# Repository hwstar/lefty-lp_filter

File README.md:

# Lefty-lp_filter
Lefty 8 Band Low Pass filter board

This is an 8 band low pass filter board for the Lefty Transceiver.

The schematic capture and pwb layout was originally done in KiCAD 5 and migrated to KiCAD 6.

The filters are individually selectable via an I2C port expander.

The filter topology used in the design is:

"Second-Harmonic Optimized Low Pass Filters" by Ed Wetherhold, W3NQN
https://www.arrl.org/files/file/Technology/tis/info/pdf/9902044.pdf

The pdf schematic file is: lp_filter_8_bands.pdf

The BOM file is: lp_filter_8_bands_BOM.csv

The gerber files are in the directory LPF_X4_FAB.

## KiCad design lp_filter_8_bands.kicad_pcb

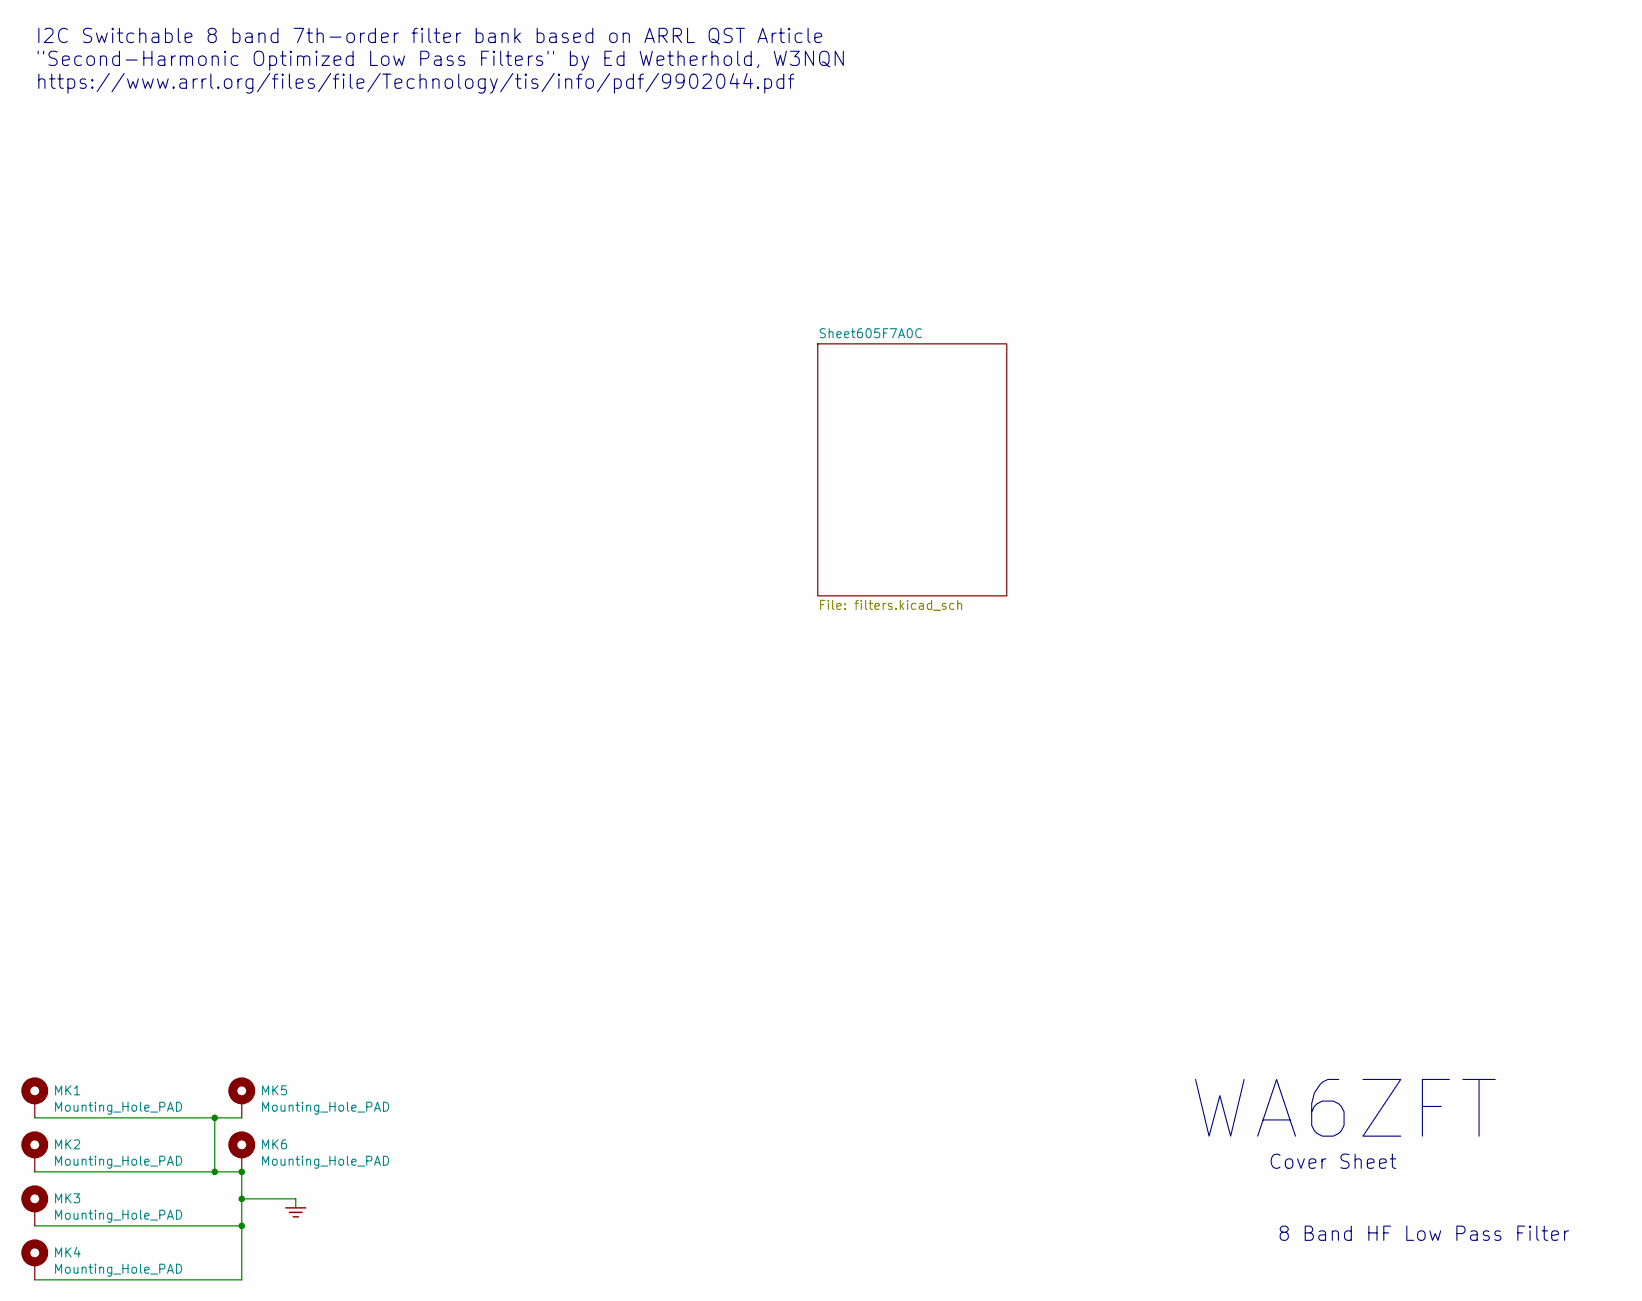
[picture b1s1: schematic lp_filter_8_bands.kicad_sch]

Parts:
MK1, MK2, MK3, MK4, MK5, MK6: Mounting_Hole_PAD; MountingHole_3.5mm_Pad_Via

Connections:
GND: MK1.1, MK2.1, MK3.1, MK4.1, MK5.1, MK6.1; also elsewhere on the board

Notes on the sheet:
WA6ZFT
Cover Sheet
I2C Switchable 8 band 7th-order filter bank based on ARRL QST Article "Second-Harmonic Optimized Low Pass Filters" by Ed Wetherhold, W3NQN https://www.arrl.org/files/file/Technology/tis/info/pdf/9902044.pdf
8 Band HF Low Pass Filter

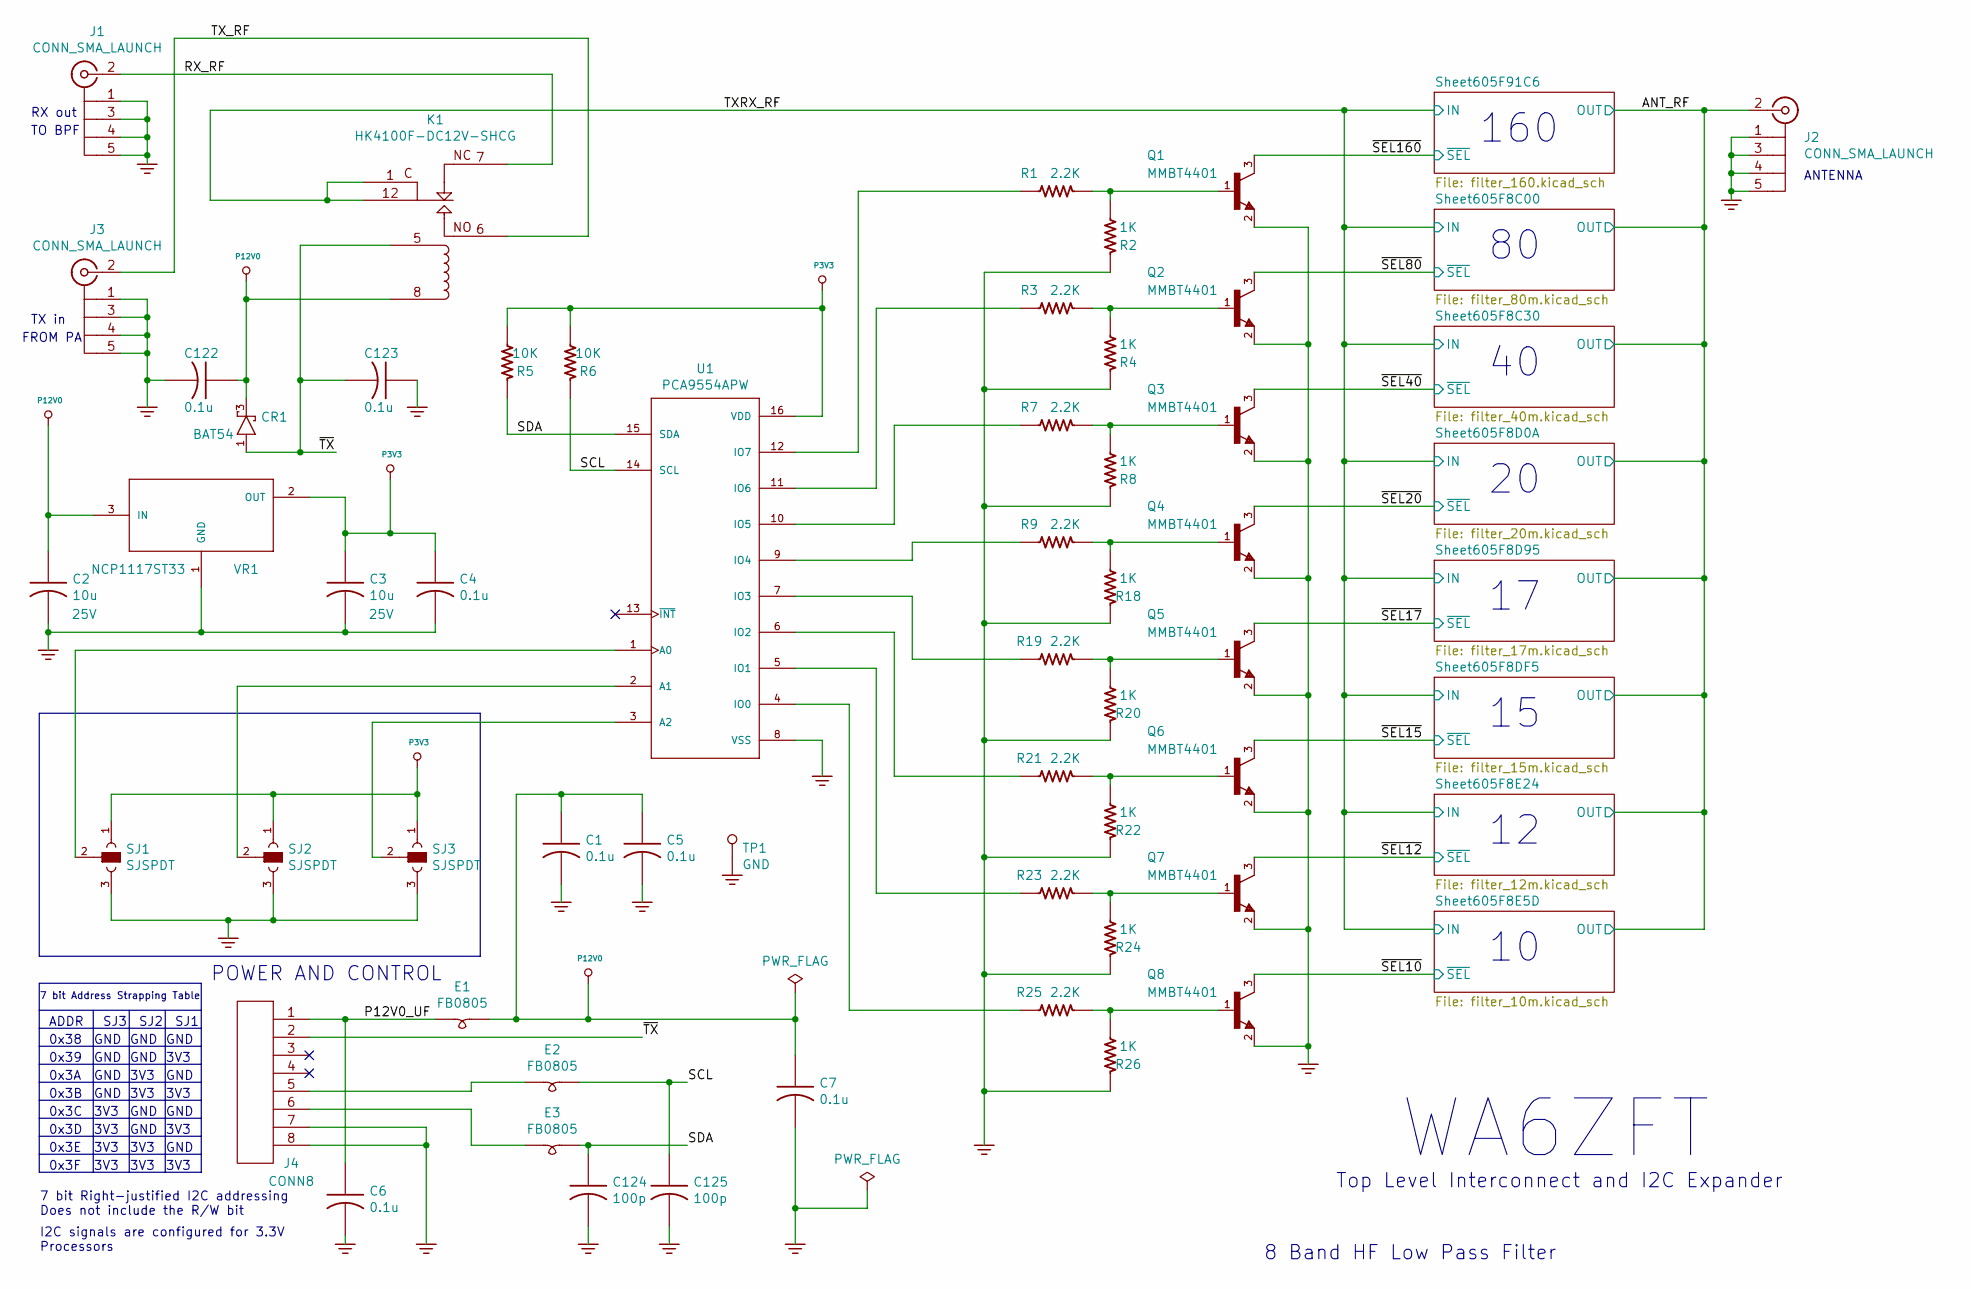
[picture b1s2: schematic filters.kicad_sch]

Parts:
C1, C4, C5, C6, C7, C122, C123: 0.1u; CC0805; PartNumber 800063-XXX
C2, C3: 10u; CC1206; Voltage 25V; PartNumber 800063-XXX
C124, C125: 100p; CC0805; PartNumber 800063-XXX
CR1: BAT54; SOT23-3-SAR-V2; PartNumber 800127-101
E1, E2, E3: FB0805; L_0805_2012Metric_Pad1.05x1.20mm_HandSolder; PartNumber 80000X-XXX
J1, J2, J3: CONN_SMA_LAUNCH; SMA_Launch_Kinghelm_KH-SMA-KE8-G; PartNumber 800233-101
J4: CONN8; JST_B8B_XH_A; PartNumber 800114-108
K1: HK4100F-DC12V-SHCG; RELAY_HK4100; PartNumber 800231-101
Q1, Q2, Q3, Q4, Q5, Q6, Q7, Q8: MMBT4401; SOT23-3-SAR-V2; PartNumber 800110-101
R1, R3, R7, R9, R19, R21, R23, R25: 2.2K; RC0805; PartNumber 800XXX-XXX
R2, R4, R8, R18, R20, R22, R24, R26: 1K; RC0805; PartNumber 800XXX-XXX
R5, R6: 10K; RC0805; PartNumber 800XXX-XXX
SJ1, SJ2, SJ3: SJSPDT
TP1: GND; TESTPIN; PartNumber 800116-101
U1: PCA9554APW; TSSOP-16_4.4x5mm_P0.65mm; PartNumber 800237-101
VR1: NCP1117ST33; SOT-223-3_TabPin2; PartNumber 800121-101

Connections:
/Sheet605F7A0C/ANT_RF: J2.2; also elsewhere on the board
/Sheet605F7A0C/P12V0_UF: C6.1, E1.1, J4.1
/Sheet605F7A0C/RX_RF: J1.2, K1.7
/Sheet605F7A0C/SCL: C125.1, E2.2, R6.1, U1.14 (SCL)
/Sheet605F7A0C/SDA: C124.1, E3.2, R5.1, U1.15 (SDA)
/Sheet605F7A0C/TXRX_RF: K1.1, K1.12; also elsewhere on the board
/Sheet605F7A0C/TX_RF: J3.2, K1.6
/Sheet605F7A0C/~SEL10: Q8.3 (C); also elsewhere on the board
/Sheet605F7A0C/~SEL12: Q7.3 (C); also elsewhere on the board
/Sheet605F7A0C/~SEL15: Q6.3 (C); also elsewhere on the board
/Sheet605F7A0C/~SEL17: Q5.3 (C); also elsewhere on the board
/Sheet605F7A0C/~SEL20: Q4.3 (C); also elsewhere on the board
/Sheet605F7A0C/~SEL40: Q3.3 (C); also elsewhere on the board
/Sheet605F7A0C/~SEL80: Q2.3 (C); also elsewhere on the board
/Sheet605F7A0C/~SEL160: Q1.3 (C); also elsewhere on the board
/Sheet605F7A0C/~TX: C123.2, CR1.1 (A), J4.2, K1.5
GND: C1.2, C2.2, C3.2, C4.2, C5.2, C6.2, C7.2, C122.2, C123.1, C124.2, C125.2, J1.1, J1.3, J1.4, J1.5, J2.1, J2.3, J2.4, J2.5, J3.1, J3.3, J3.4, J3.5, J4.7, J4.8, Q1.2 (E), Q2.2 (E), Q3.2 (E), Q4.2 (E), Q5.2 (E), Q6.2 (E), Q7.2 (E), Q8.2 (E), R2.1, R4.1, R8.1, R18.1, R20.1, R22.1, R24.1, R26.1, SJ1.3, SJ2.3, SJ3.3, TP1.1 (TP), U1.8 (VSS), VR1.1 (GND); also elsewhere on the board
unnamed: E2.1, J4.5
unnamed: E3.1, J4.6
unnamed: Q1.1 (B), R1.1, R2.2
unnamed: Q2.1 (B), R3.1, R4.2
unnamed: Q3.1 (B), R7.1, R8.2
unnamed: Q4.1 (B), R9.1, R18.2
unnamed: Q5.1 (B), R19.1, R20.2
unnamed: Q6.1 (B), R21.1, R22.2
unnamed: Q7.1 (B), R23.1, R24.2
unnamed: Q8.1 (B), R25.1, R26.2
unnamed: R1.2, U1.12 (IO7)
unnamed: R3.2, U1.11 (IO6)
unnamed: R7.2, U1.10 (IO5)
unnamed: R9.2, U1.9 (IO4)
unnamed: R19.2, U1.7 (IO3)
unnamed: R21.2, U1.6 (IO2)
unnamed: R23.2, U1.5 (IO1)
unnamed: R25.2, U1.4 (IO0)
unnamed: SJ1.2, U1.1 (A0)
unnamed: SJ2.2, U1.2 (A1)
unnamed: SJ3.2, U1.3 (A2)
P3V3: C3.1, C4.1, R5.2, R6.2, SJ1.1, SJ2.1, SJ3.1, U1.16 (VDD), VR1.2 (OUT)
P12V0: C1.1, C2.1, C5.1, C7.1, C122.1, CR1.3 (C), E1.2, K1.8, VR1.3 (IN); also elsewhere on the board

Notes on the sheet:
GND
SJ2
3V3
0x3A
0x3E
0x3B
0x39
0x3D
ADDR
160
8 Band HF Low Pass Filter
7 bit Address Strapping Table
TX in
SJ3
I2C signals are configured for 3.3V Processors
Top Level Interconnect and I2C Expander
RX out
GND
7 bit Right-justified I2C addressing Does not include the R/W bit
0x3F
WA6ZFT
SJ1
0x38
FROM PA
POWER AND CONTROL
TO BPF
0x3C
ANTENNA

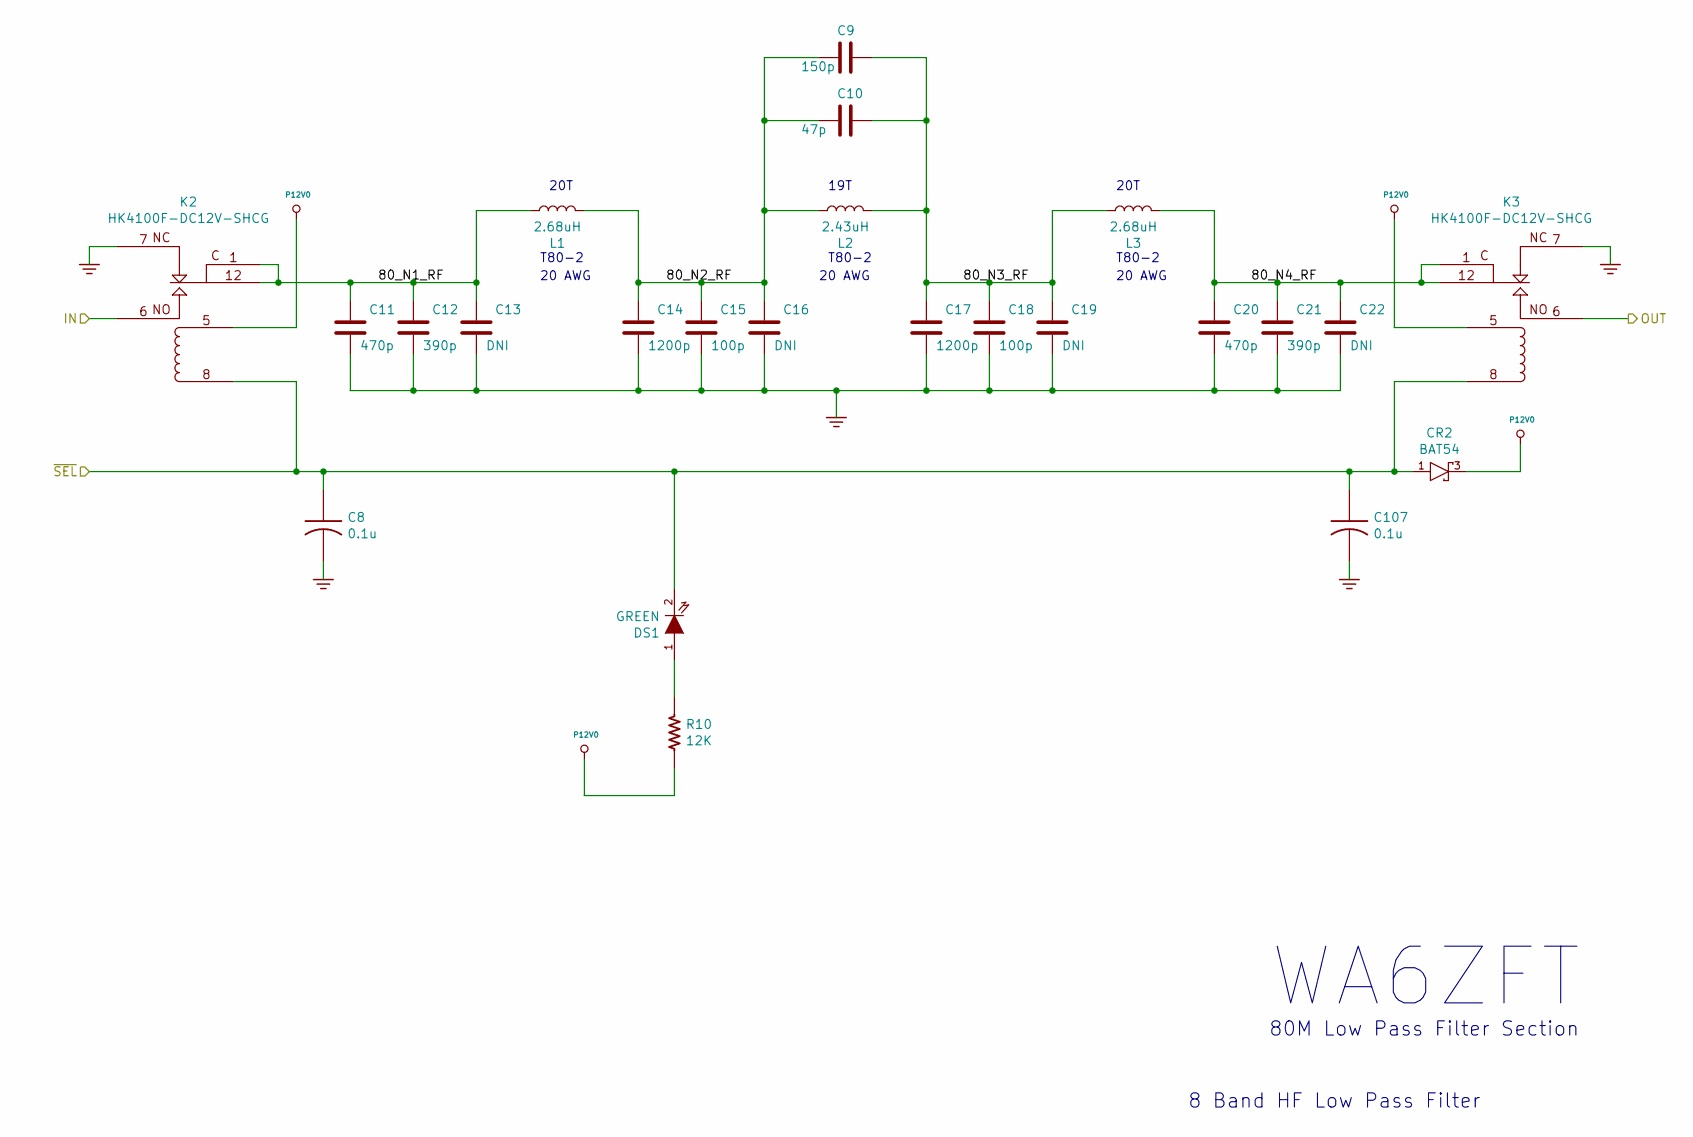
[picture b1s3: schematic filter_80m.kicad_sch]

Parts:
C8, C107: 0.1u; CC0805; PartNumber 800063-XXX
C9: 150p; CC0805; PartNumber 800232-151
C10: 47p; CC0805; PartNumber 800232-470
C11, C20: 470p; CC0805; PartNumber 800232-471
C12, C21: 390p; CC0805; PartNumber 800232-391
C13, C16, C19, C22: DNI; CC0805; PartNumber 800XXX-XXX
C14, C17: 1200p; CC0805; PartNumber 800232-122
C15, C18: 100p; CC0805; PartNumber 800232-101
CR2: BAT54; SOT23-3-SAR-V2; PartNumber 800127-101
DS1: GREEN; LED0805; PartNumber 800113-102
K2, K3: HK4100F-DC12V-SHCG; RELAY_HK4100; PartNumber 800231-101
L1, L3: 2.68uH; TOROID_T80_VERT; PartNumber 800234-802
L2: 2.43uH; TOROID_T80_VERT; PartNumber 800234-802
R10: 12K; RC0805; PartNumber 800XXX-XXX

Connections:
/Sheet605F7A0C/ANT_RF: K3.6; also elsewhere on the board
/Sheet605F7A0C/Sheet605F8C00/80_N1_RF: C11.1, C12.1, C13.1, K2.1, K2.12, L1.1
/Sheet605F7A0C/Sheet605F8C00/80_N2_RF: C9.2, C10.2, C14.1, C15.1, C16.1, L1.2, L2.1
/Sheet605F7A0C/Sheet605F8C00/80_N3_RF: C9.1, C10.1, C17.1, C18.1, C19.1, L2.2, L3.1
/Sheet605F7A0C/Sheet605F8C00/80_N4_RF: C20.1, C21.1, C22.1, K3.1, K3.12, L3.2
/Sheet605F7A0C/TXRX_RF: K2.6; also elsewhere on the board
/Sheet605F7A0C/~SEL80: C8.1, C107.1, CR2.1 (A), DS1.2 (K), K2.8, K3.8; also elsewhere on the board
GND: C8.2, C11.2, C12.2, C13.2, C14.2, C15.2, C16.2, C17.2, C18.2, C19.2, C20.2, C21.2, C22.2, C107.2, K2.7, K3.7; also elsewhere on the board
unnamed: DS1.1 (A), R10.1
P12V0: CR2.3 (C), K2.5, K3.5, R10.2; also elsewhere on the board

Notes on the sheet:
20 AWG
20T
8 Band HF Low Pass Filter
T80-2
19T
80M Low Pass Filter Section
WA6ZFT

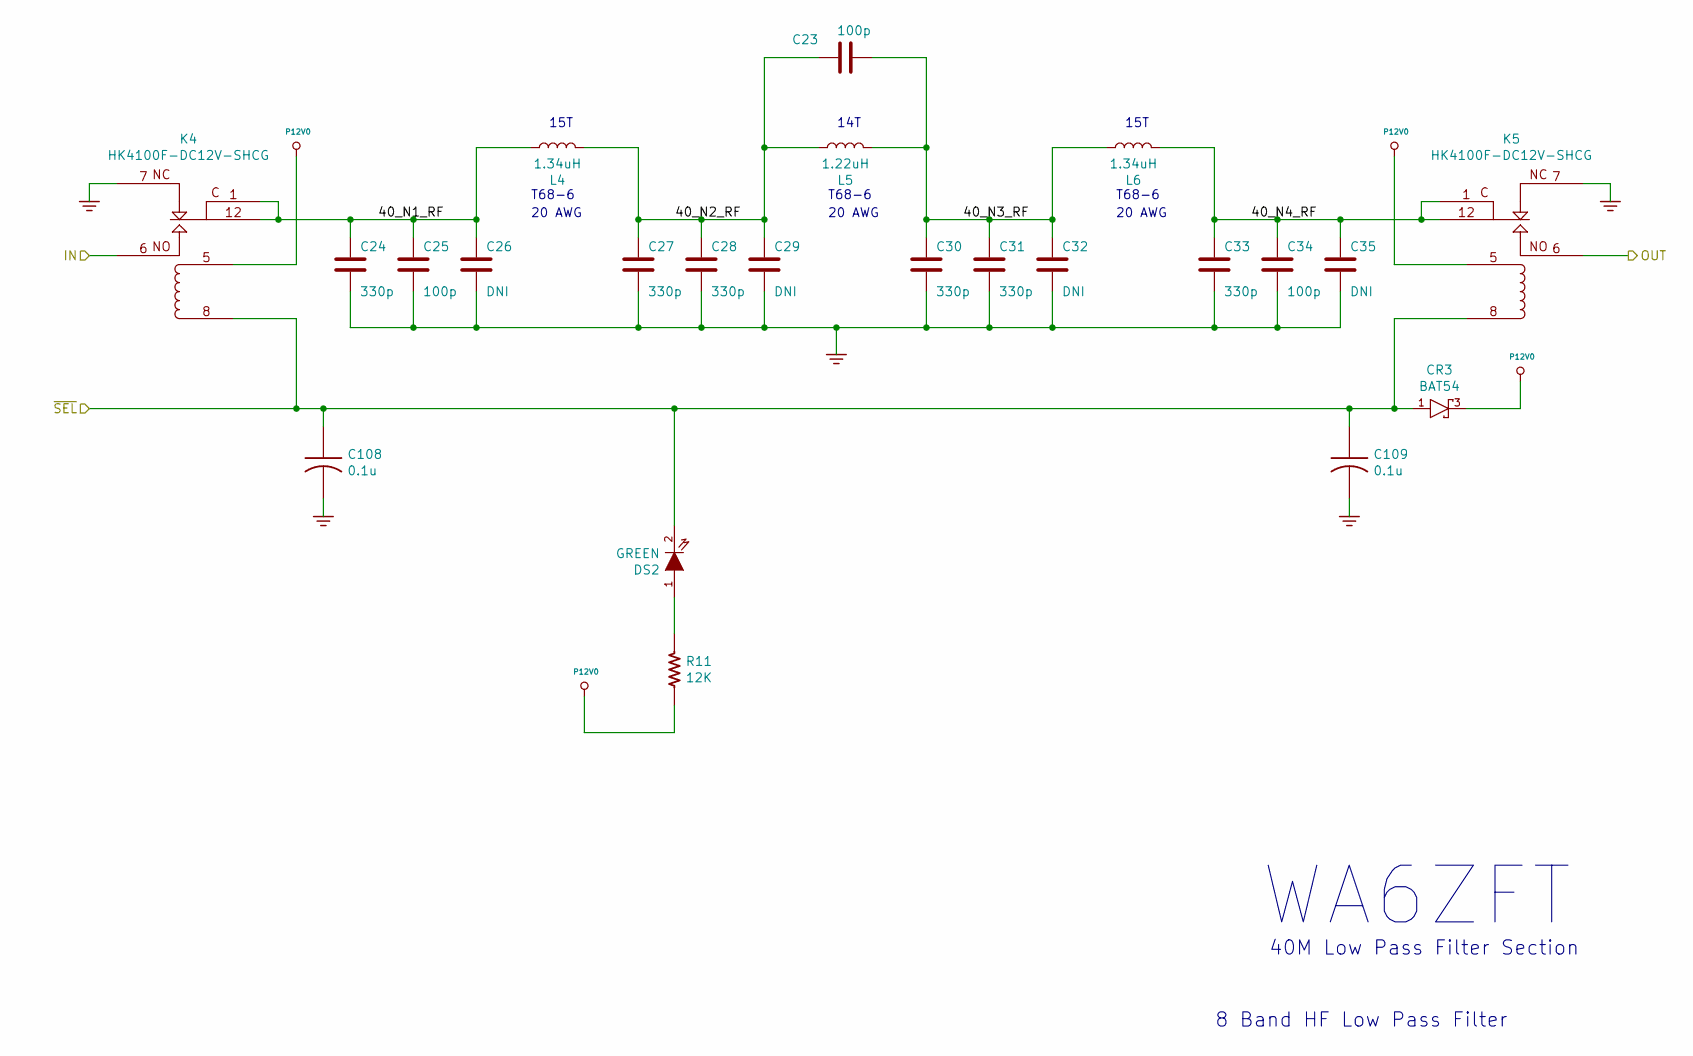
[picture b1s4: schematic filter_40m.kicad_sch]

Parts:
C23, C25, C34: 100p; CC0805; PartNumber 800232-101
C24, C27, C28, C30, C31, C33: 330p; CC0805; PartNumber 800232-331
C26, C29, C32, C35: DNI; CC0805; PartNumber 800XXX-XXX
C108, C109: 0.1u; CC0805; PartNumber 800063-XXX
CR3: BAT54; SOT23-3-SAR-V2; PartNumber 800127-101
DS2: GREEN; LED0805; PartNumber 800113-102
K4, K5: HK4100F-DC12V-SHCG; RELAY_HK4100; PartNumber 800231-101
L4, L6: 1.34uH; TOROID_T68_VERT; PartNumber 800234-686
L5: 1.22uH; TOROID_T68_VERT; PartNumber 800234-686
R11: 12K; RC0805; PartNumber 800XXX-XXX

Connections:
/Sheet605F7A0C/ANT_RF: K5.6; also elsewhere on the board
/Sheet605F7A0C/Sheet605F8C30/40_N1_RF: C24.1, C25.1, C26.1, K4.1, K4.12, L4.1
/Sheet605F7A0C/Sheet605F8C30/40_N2_RF: C23.2, C27.1, C28.1, C29.1, L4.2, L5.1
/Sheet605F7A0C/Sheet605F8C30/40_N3_RF: C23.1, C30.1, C31.1, C32.1, L5.2, L6.1
/Sheet605F7A0C/Sheet605F8C30/40_N4_RF: C33.1, C34.1, C35.1, K5.1, K5.12, L6.2
/Sheet605F7A0C/TXRX_RF: K4.6; also elsewhere on the board
/Sheet605F7A0C/~SEL40: C108.1, C109.1, CR3.1 (A), DS2.2 (K), K4.8, K5.8; also elsewhere on the board
GND: C24.2, C25.2, C26.2, C27.2, C28.2, C29.2, C30.2, C31.2, C32.2, C33.2, C34.2, C35.2, C108.2, C109.2, K4.7, K5.7; also elsewhere on the board
unnamed: DS2.1 (A), R11.1
P12V0: CR3.3 (C), K4.5, K5.5, R11.2; also elsewhere on the board

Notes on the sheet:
T68-6
40M Low Pass Filter Section
15T
8 Band HF Low Pass Filter
20 AWG
WA6ZFT
14T
15T

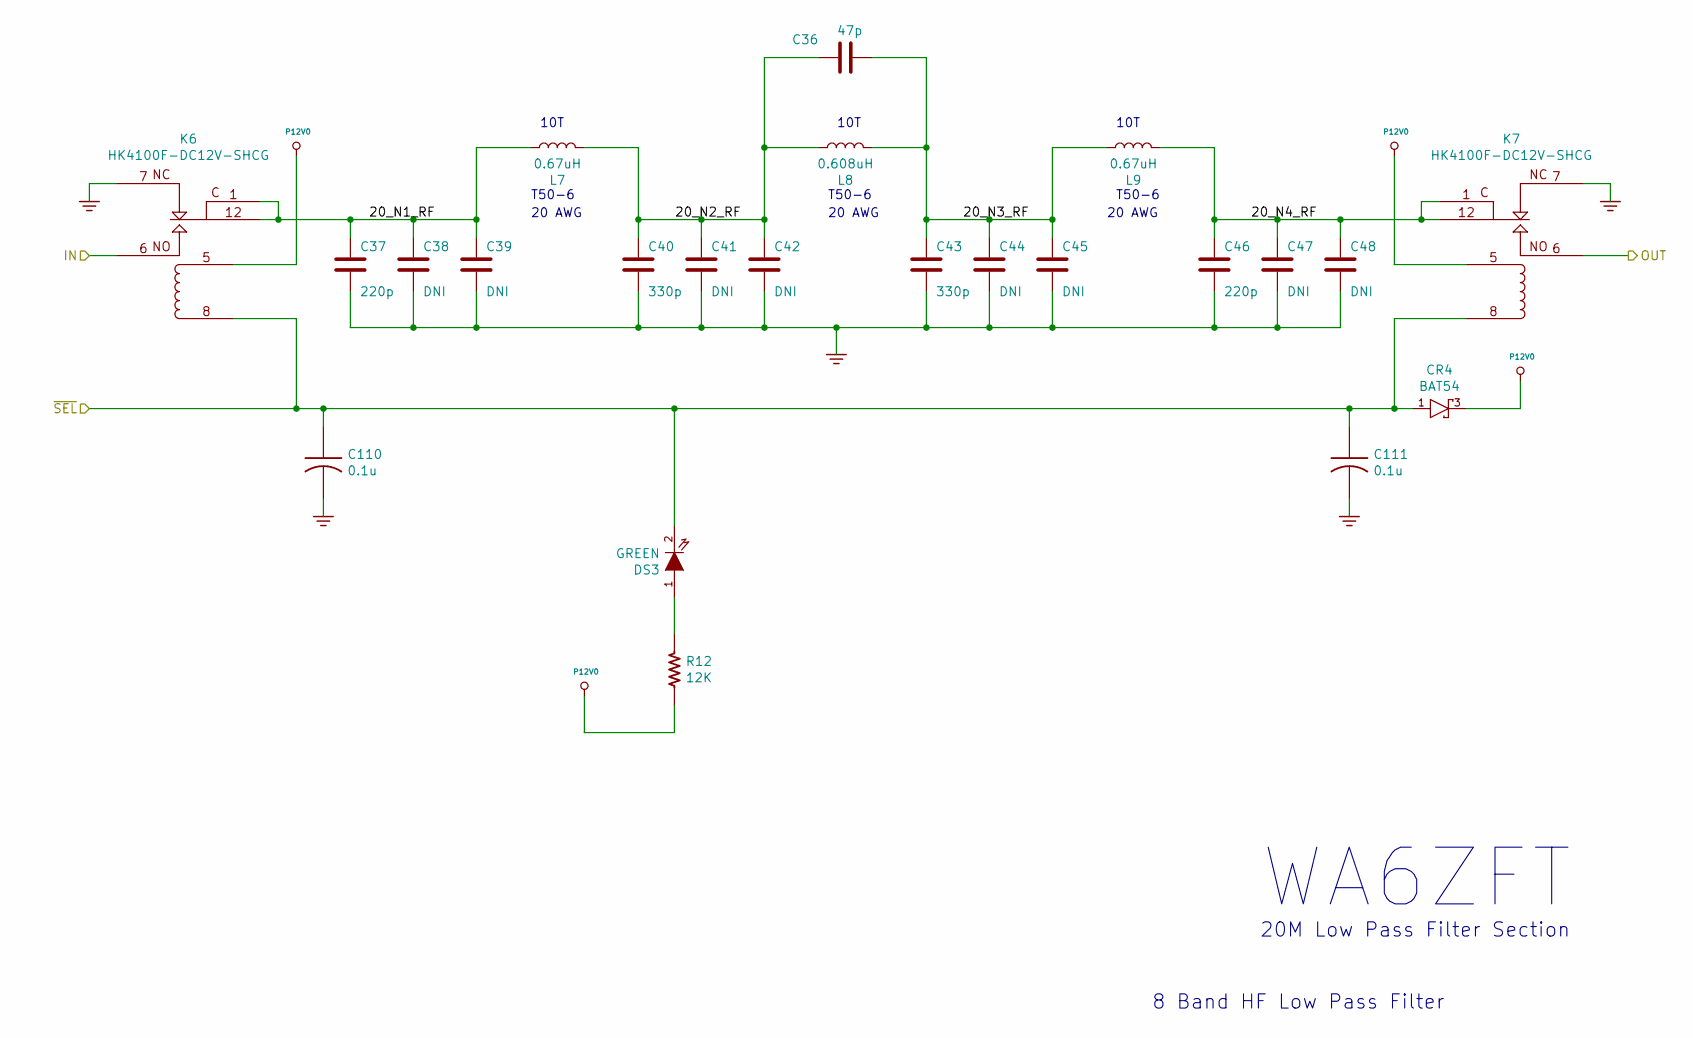
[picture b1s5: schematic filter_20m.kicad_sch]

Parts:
C36: 47p; CC0805; PartNumber 800232-470
C37, C46: 220p; CC0805; PartNumber 800232-221
C38, C39, C41, C42, C44, C45, C47, C48: DNI; CC0805; PartNumber 800XXX-XXX
C40, C43: 330p; CC0805; PartNumber 800232-331
C110, C111: 0.1u; CC0805; PartNumber 800063-XXX
CR4: BAT54; SOT23-3-SAR-V2; PartNumber 800127-101
DS3: GREEN; LED0805; PartNumber 800113-102
K6, K7: HK4100F-DC12V-SHCG; RELAY_HK4100; PartNumber 800231-101
L7, L9: 0.67uH; TOROID_T50_VERT; PartNumber 800234-506
L8: 0.608uH; TOROID_T50_VERT; PartNumber 800234-506
R12: 12K; RC0805; PartNumber 800XXX-XXX

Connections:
/Sheet605F7A0C/ANT_RF: K7.6; also elsewhere on the board
/Sheet605F7A0C/Sheet605F8D0A/20_N1_RF: C37.1, C38.1, C39.1, K6.1, K6.12, L7.1
/Sheet605F7A0C/Sheet605F8D0A/20_N2_RF: C36.2, C40.1, C41.1, C42.1, L7.2, L8.1
/Sheet605F7A0C/Sheet605F8D0A/20_N3_RF: C36.1, C43.1, C44.1, C45.1, L8.2, L9.1
/Sheet605F7A0C/Sheet605F8D0A/20_N4_RF: C46.1, C47.1, C48.1, K7.1, K7.12, L9.2
/Sheet605F7A0C/TXRX_RF: K6.6; also elsewhere on the board
/Sheet605F7A0C/~SEL20: C110.1, C111.1, CR4.1 (A), DS3.2 (K), K6.8, K7.8; also elsewhere on the board
GND: C37.2, C38.2, C39.2, C40.2, C41.2, C42.2, C43.2, C44.2, C45.2, C46.2, C47.2, C48.2, C110.2, C111.2, K6.7, K7.7; also elsewhere on the board
unnamed: DS3.1 (A), R12.1
P12V0: CR4.3 (C), K6.5, K7.5, R12.2; also elsewhere on the board

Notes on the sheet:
20 AWG
WA6ZFT
10T
20M Low Pass Filter Section
T50-6
8 Band HF Low Pass Filter
10T

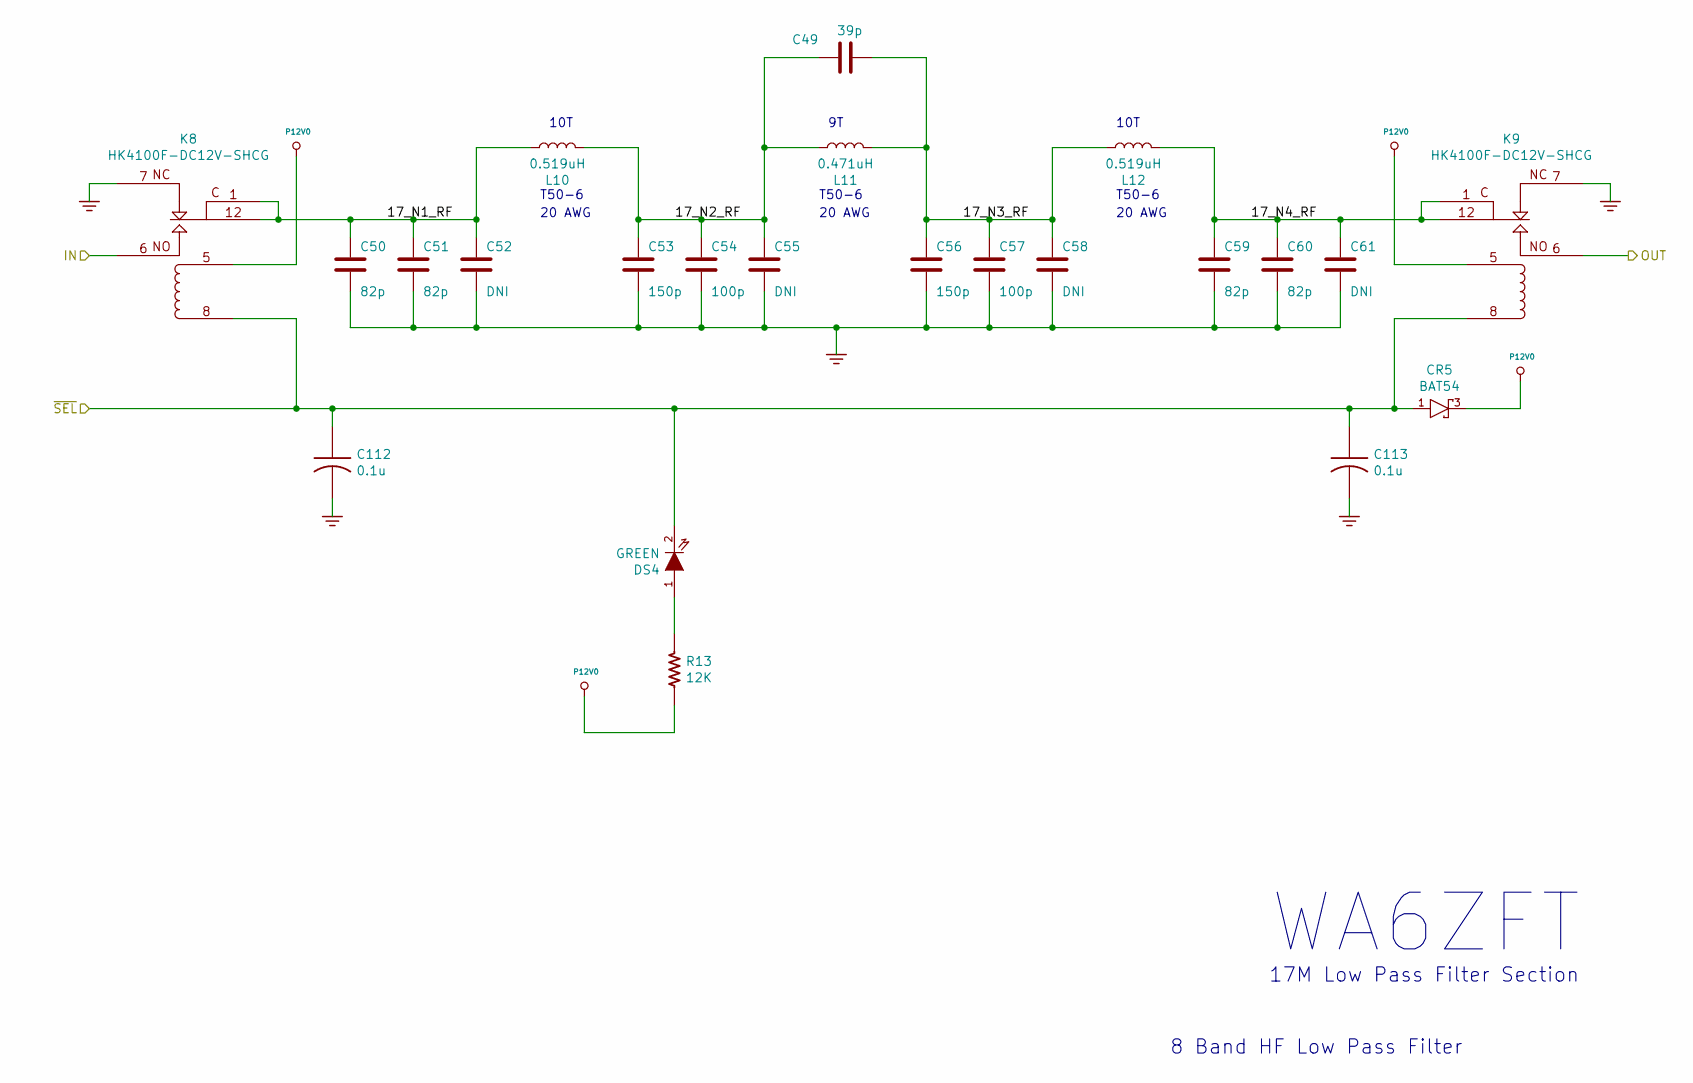
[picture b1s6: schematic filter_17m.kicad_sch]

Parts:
C49: 39p; CC0805; PartNumber 800232-390
C50, C51, C59, C60: 82p; CC0805; PartNumber 800232-820
C52, C55, C58, C61: DNI; CC0805; PartNumber 800XXX-XXX
C53, C56: 150p; CC0805; PartNumber 800232-151
C54, C57: 100p; CC0805; PartNumber 800232-101
C112, C113: 0.1u; CC0805; PartNumber 800063-XXX
CR5: BAT54; SOT23-3-SAR-V2; PartNumber 800127-101
DS4: GREEN; LED0805; PartNumber 800113-102
K8, K9: HK4100F-DC12V-SHCG; RELAY_HK4100; PartNumber 800231-101
L10, L12: 0.519uH; TOROID_T50_VERT; PartNumber 800234-506
L11: 0.471uH; TOROID_T50_VERT; PartNumber 800234-506
R13: 12K; RC0805; PartNumber 800XXX-XXX

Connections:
/Sheet605F7A0C/ANT_RF: K9.6; also elsewhere on the board
/Sheet605F7A0C/Sheet605F8D95/17_N1_RF: C50.1, C51.1, C52.1, K8.1, K8.12, L10.1
/Sheet605F7A0C/Sheet605F8D95/17_N2_RF: C49.2, C53.1, C54.1, C55.1, L10.2, L11.1
/Sheet605F7A0C/Sheet605F8D95/17_N3_RF: C49.1, C56.1, C57.1, C58.1, L11.2, L12.1
/Sheet605F7A0C/Sheet605F8D95/17_N4_RF: C59.1, C60.1, C61.1, K9.1, K9.12, L12.2
/Sheet605F7A0C/TXRX_RF: K8.6; also elsewhere on the board
/Sheet605F7A0C/~SEL17: C112.1, C113.1, CR5.1 (A), DS4.2 (K), K8.8, K9.8; also elsewhere on the board
GND: C50.2, C51.2, C52.2, C53.2, C54.2, C55.2, C56.2, C57.2, C58.2, C59.2, C60.2, C61.2, C112.2, C113.2, K8.7, K9.7; also elsewhere on the board
unnamed: DS4.1 (A), R13.1
P12V0: CR5.3 (C), K8.5, K9.5, R13.2; also elsewhere on the board

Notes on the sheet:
WA6ZFT
20 AWG
T50-6
17M Low Pass Filter Section
10T
10T
8 Band HF Low Pass Filter

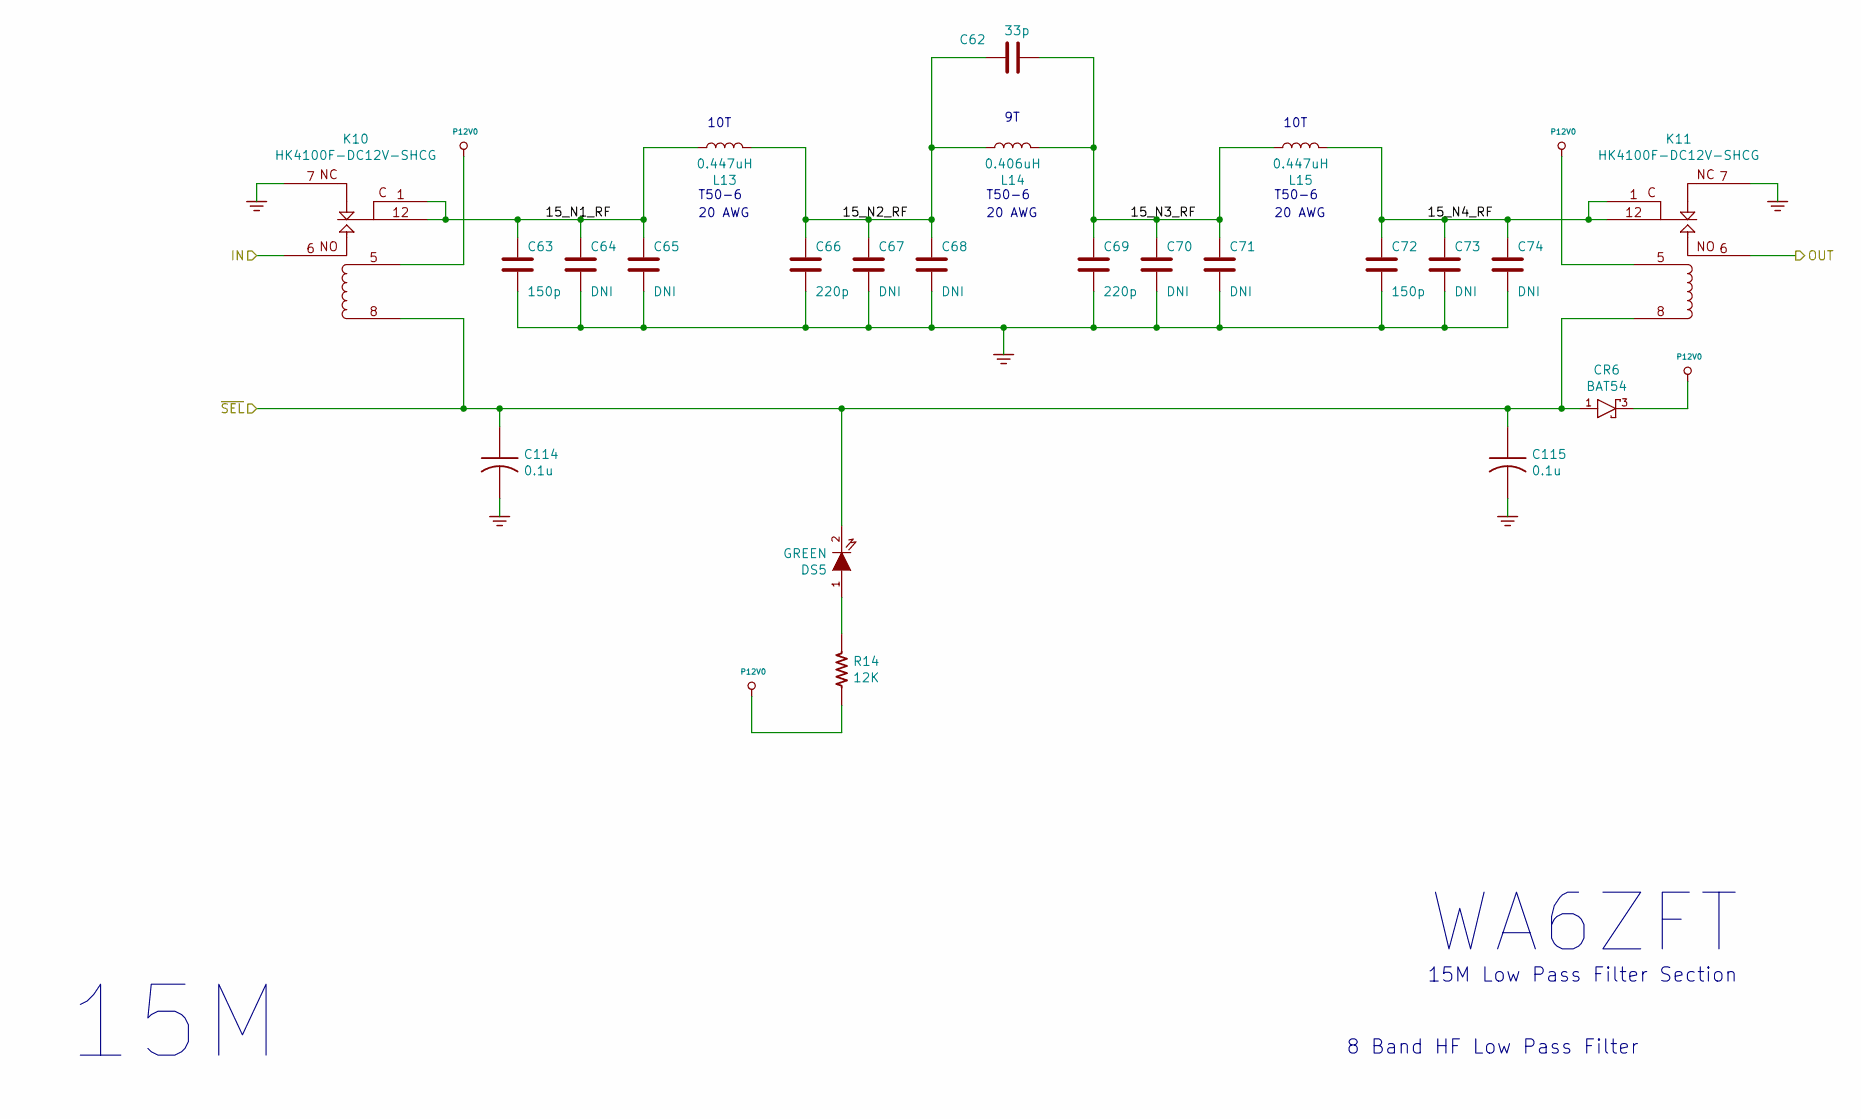
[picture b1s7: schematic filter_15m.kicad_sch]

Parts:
C62: 33p; CC0805; PartNumber 800232-330
C63, C72: 150p; CC0805; PartNumber 800232-151
C64, C65, C67, C68, C70, C71, C73, C74: DNI; CC0805; PartNumber 800XXX-XXX
C66, C69: 220p; CC0805; PartNumber 800232-221
C114, C115: 0.1u; CC0805; PartNumber 800063-XXX
CR6: BAT54; SOT23-3-SAR-V2; PartNumber 800127-101
DS5: GREEN; LED0805; PartNumber 800113-102
K10, K11: HK4100F-DC12V-SHCG; RELAY_HK4100; PartNumber 800231-101
L13, L15: 0.447uH; TOROID_T50_VERT; PartNumber 800234-506
L14: 0.406uH; TOROID_T50_VERT; PartNumber 800234-506
R14: 12K; RC0805; PartNumber 800XXX-XXX

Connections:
/Sheet605F7A0C/ANT_RF: K11.6; also elsewhere on the board
/Sheet605F7A0C/Sheet605F8DF5/15_N1_RF: C63.1, C64.1, C65.1, K10.1, K10.12, L13.1
/Sheet605F7A0C/Sheet605F8DF5/15_N2_RF: C62.2, C66.1, C67.1, C68.1, L13.2, L14.1
/Sheet605F7A0C/Sheet605F8DF5/15_N3_RF: C62.1, C69.1, C70.1, C71.1, L14.2, L15.1
/Sheet605F7A0C/Sheet605F8DF5/15_N4_RF: C72.1, C73.1, C74.1, K11.1, K11.12, L15.2
/Sheet605F7A0C/TXRX_RF: K10.6; also elsewhere on the board
/Sheet605F7A0C/~SEL15: C114.1, C115.1, CR6.1 (A), DS5.2 (K), K10.8, K11.8; also elsewhere on the board
GND: C63.2, C64.2, C65.2, C66.2, C67.2, C68.2, C69.2, C70.2, C71.2, C72.2, C73.2, C74.2, C114.2, C115.2, K10.7, K11.7; also elsewhere on the board
unnamed: DS5.1 (A), R14.1
P12V0: CR6.3 (C), K10.5, K11.5, R14.2; also elsewhere on the board

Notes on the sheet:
20 AWG
T50-6
10T
15M Low Pass Filter Section
15M
8 Band HF Low Pass Filter
10T
WA6ZFT

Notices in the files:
lp_filter_8_bands.kicad_pcb:
Copyright (C) 2022 Stephen Rodgers
